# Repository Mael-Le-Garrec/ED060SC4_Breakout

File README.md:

# ED060SC4 Breakout Board

This PCB is intended as a breakout board for the connector of the epaper screen ED060SC4.
This simple board has been inspired by [EPDiy](https://github.com/vroland/epdiy), where the
symbol and footprint for the connector come from. 

# Images

- 3D View

- Schematic

# Making the board

## Buying Components

Only two components are needed:
- The screen connector
- Headers

The screen connector is manufactured by Hirose and can be found under the
reference `FH26W-39S-0.3SHW`, for example on 
[LCSC](https://www.lcsc.com/product-detail/FFC-FPC-Connectors_HRS-Hirose-FH26W-39S-0-3SHW-60_C92280.html).

The headers have a standard pitch of 2.54mm and can be easily found on aliexpress for a cheap price.
The style is at your convenience, you're probably going to have to choose between male pin headers 
or female socket headers, as described on [Wikipedia](https://en.wikipedia.org/wiki/Pin_header)

## Having the board manufactured

The [gerbers file](./gerbers/gerbers.zip) can be directly uploaded on manufacturers' websites.

JLCPCB has a special price (at the time of writing, 2023-04-01) on boards smaller than
102x102 mm. This breakout board falls just under this condition, making the price
quite interesting.
At the time of writing, 5 of those board cost 1.88€ on JLCPCB + shipping.

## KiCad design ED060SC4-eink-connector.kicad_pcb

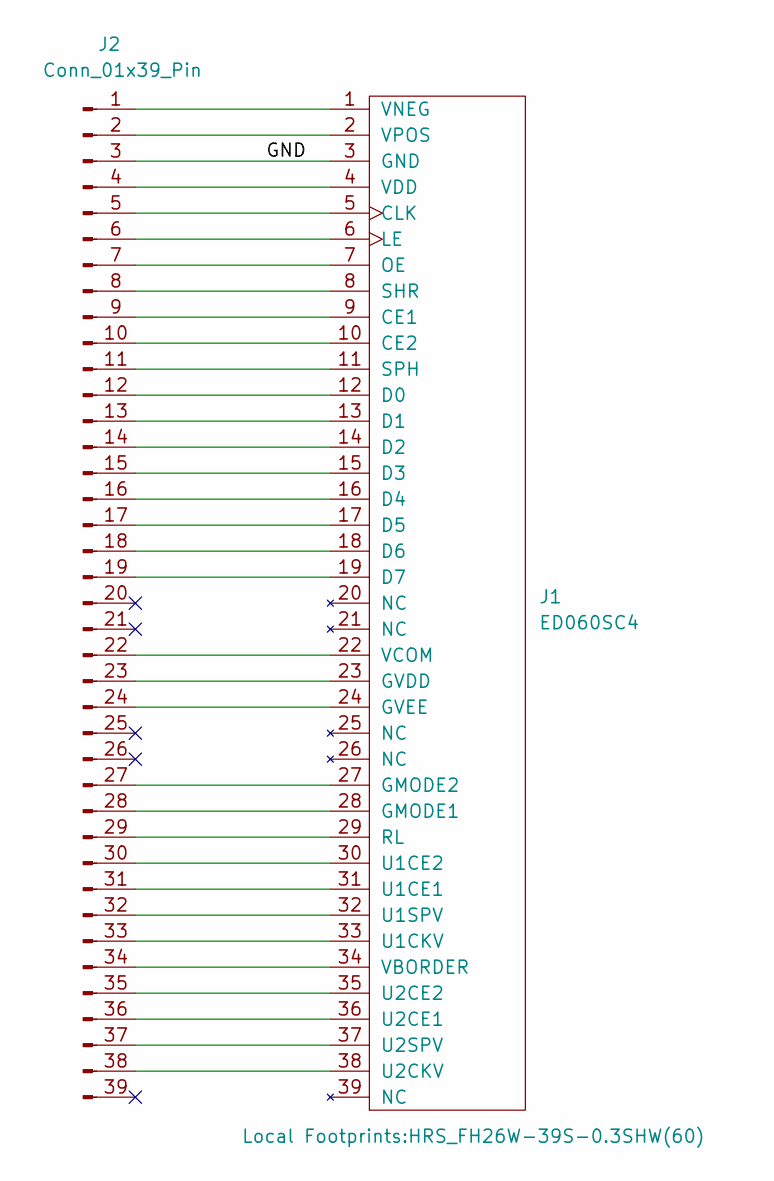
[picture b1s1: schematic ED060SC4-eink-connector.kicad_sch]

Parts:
J1: ED060SC4; HRS_FH26W-39S-0.3SHW(60)
J2: Conn_01x39_Pin; PinHeader_1x39_P2.54mm_Vertical

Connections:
/GND: J1.3 (GND), J2.3
unnamed: J1.9 (CE1), J2.9
unnamed: J1.10 (CE2), J2.10
unnamed: J1.5 (CLK), J2.5
unnamed: J1.12 (D0), J2.12
unnamed: J1.13 (D1), J2.13
unnamed: J1.14 (D2), J2.14
unnamed: J1.15 (D3), J2.15
unnamed: J1.16 (D4), J2.16
unnamed: J1.17 (D5), J2.17
unnamed: J1.18 (D6), J2.18
unnamed: J1.19 (D7), J2.19
unnamed: J1.28 (GMODE1), J2.28
unnamed: J1.27 (GMODE2), J2.27
unnamed: J1.23 (GVDD), J2.23
unnamed: J1.24 (GVEE), J2.24
unnamed: J1.6 (LE), J2.6
unnamed: J1.7 (OE), J2.7
unnamed: J1.29 (RL), J2.29
unnamed: J1.8 (SHR), J2.8
unnamed: J1.11 (SPH), J2.11
unnamed: J1.31 (U1CE1), J2.31
unnamed: J1.30 (U1CE2), J2.30
unnamed: J1.33 (U1CKV), J2.33
unnamed: J1.32 (U1SPV), J2.32
unnamed: J1.36 (U2CE1), J2.36
unnamed: J1.35 (U2CE2), J2.35
unnamed: J1.38 (U2CKV), J2.38
unnamed: J1.37 (U2SPV), J2.37
unnamed: J1.34 (VBORDER), J2.34
unnamed: J1.22 (VCOM), J2.22
unnamed: J1.4 (VDD), J2.4
unnamed: J1.1 (VNEG), J2.1
unnamed: J1.2 (VPOS), J2.2

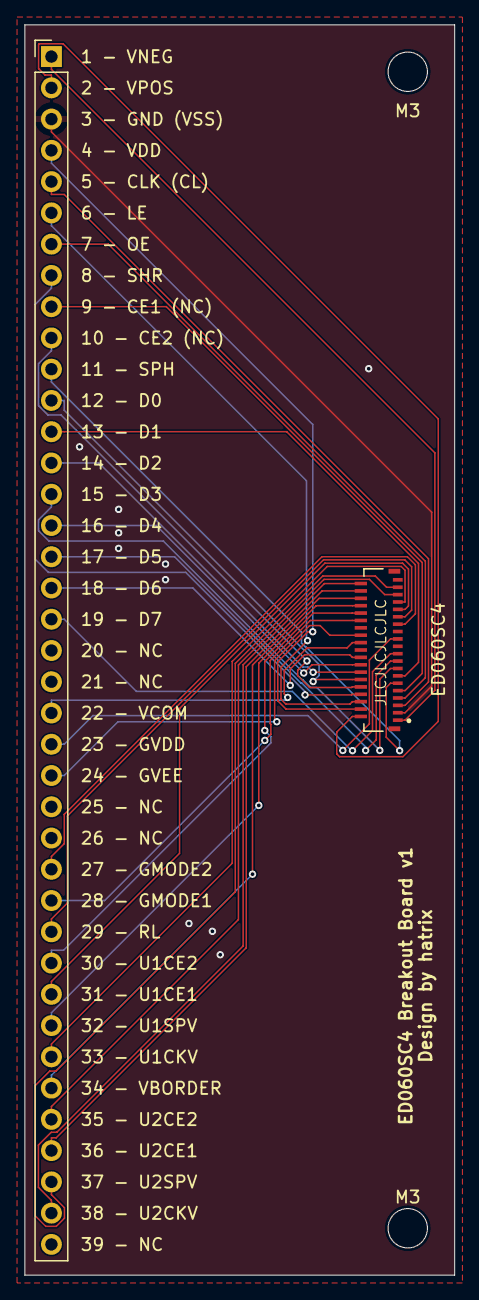
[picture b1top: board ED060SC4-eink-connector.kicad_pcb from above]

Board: 2 copper layers, 34.9 x 101.6 mm, 4 parts (0 on the bottom side), 34 nets.

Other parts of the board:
M3, M3#2: MountingHole_3.2mm_M3

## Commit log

2023-03-31 First version of the project
2023-03-31 Fix typo in README
2023-03-31 Add a few vias for ground plane
2023-03-31 Add mounting holes
2023-03-31 update 3D view
2023-04-01 Add original datasheet name for PIN3 (VSS & GND)
2023-04-01 Value of the connector was not plotted
2023-04-01 Add custom location for JLCPCB's order number
